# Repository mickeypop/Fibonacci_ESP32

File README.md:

# Fibonacci Clock with ESP32 WiFi
ESP32 Atomic Fibonacci Clock with Android App and full Daylight Savings Time(DST) support

Unlike other Fibonacci Clocks, this is fully Atomic.  
Just set WiFi and a few presets with the first Arduino preset sketch to set preferances then compile the main sketch.

I also gave it minute accuracy, most Fibonacci Clocks can only show within 5 minutes.  4 Extra LEDs place the minutes that do not end in 0 or 5.

I added I2C LCD support for debugging but is not needed in use.

With mDNS support you can access it by web page or Android app as **fibonacci.local** once it is on your WiFi network.

Just choose your Time Zone and the DST rule that applies to you and the clock time is set.

Because I used the preferances library this will not work on the ESP8266 but with the Preferances replaced with file system and say JSON this could be adapted easily.

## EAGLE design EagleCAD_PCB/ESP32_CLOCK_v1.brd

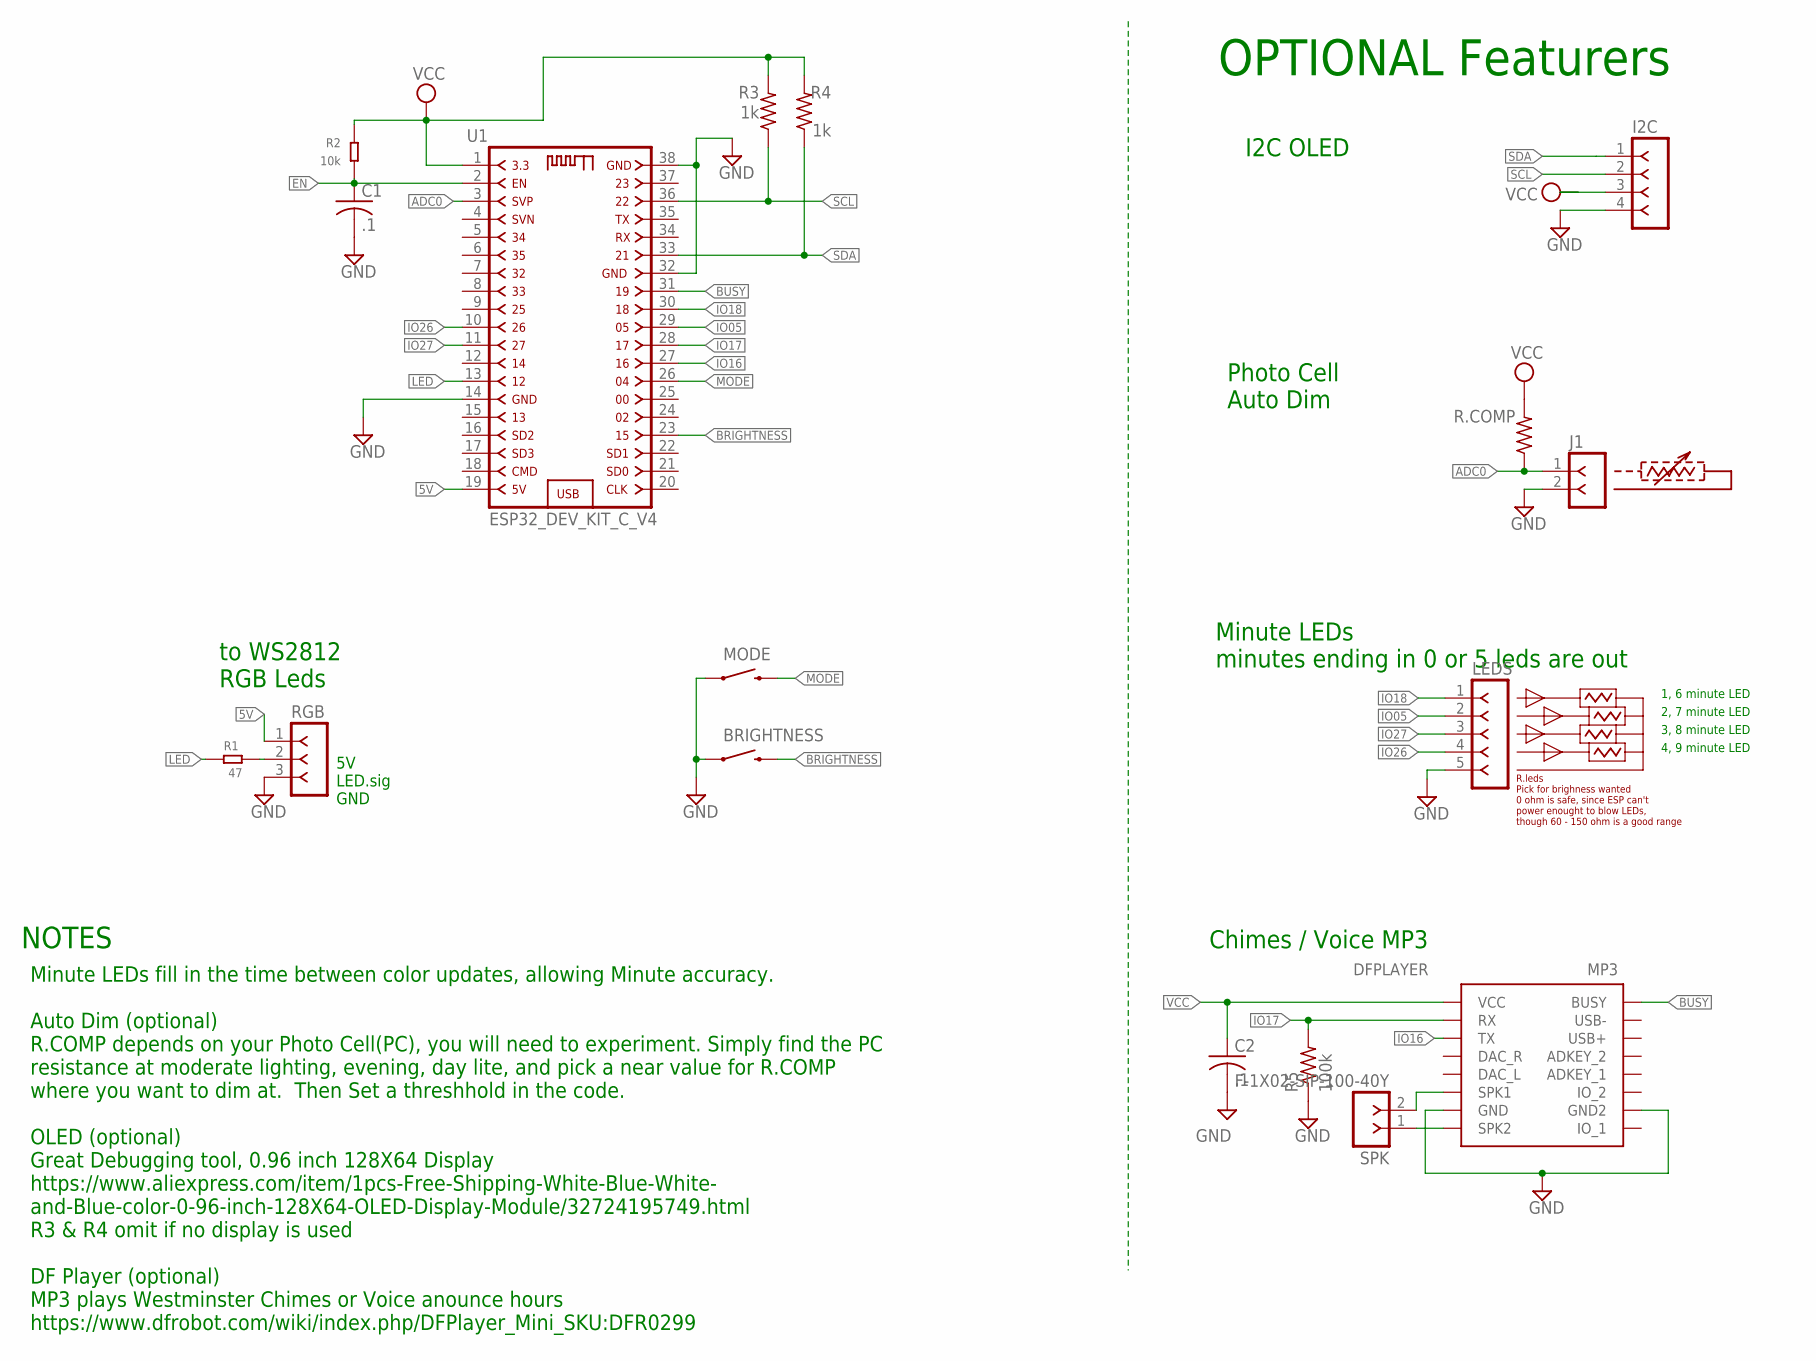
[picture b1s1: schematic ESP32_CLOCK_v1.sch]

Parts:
BRIGHTNESS: SWITCH-MOMENTARY-2SIDE_EZ; TACTILE-PTH-SIDEEZ
C1, C2: .1; C0805K
I2C: F-1X04-SIP-100-40Y; SIP-100-04-40Y
J1: F-1X02-SIP-100-40Y; SIP-100-02-40Y
LEDS: F-1X05-SIP-100-40Y; SIP-100-05-40Y
MODE: SWITCH-MOMENTARY-2SIDE_EZ; TACTILE-PTH-SIDEEZ
MP3: DFPLAYER
R1: 47; R0805
R2: 10k; R0805
R3, R4: 1k; M0805
R5: 100k; M0805
R.COMP: R-US_M0805; M0805
RGB: F-1X03-SIP-100-40Y; SIP-100-03-40Y
SPK: F-1X02-SIP-100-40Y; SIP-100-02-40Y
U1: ESP32_DEV_KIT_C_V4

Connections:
5V: RGB.1, U1.19
ADC0: J1.1, R.COMP.1, U1.3
BRIGHTNESS: BRIGHTNESS.2, U1.23
BUSY: MP3.BUSY, U1.31
EN: C1.1, R2.1, U1.2
GND: BRIGHTNESS.1, C1.2, C2.2, I2C.4, J1.2, LEDS.5, MODE.1, MP3.GND, MP3.GND2, R5.1, RGB.3, U1.14, U1.32, U1.38
IO05: LEDS.2, U1.29
IO16: MP3.TX, U1.27
IO17: MP3.RX, R5.2, U1.28
IO18: LEDS.1, U1.30
IO26: LEDS.4, U1.10
IO27: LEDS.3, U1.11
LED: R1.2, U1.13
MODE: MODE.2, U1.26
unnamed: MP3.SPK2, SPK.1
unnamed: MP3.SPK1, SPK.2
unnamed: R1.1, RGB.2
SCL: I2C.2, R3.1, U1.36
SDA: I2C.1, R4.1, U1.33
VCC: C2.1, I2C.3, MP3.VCC, R2.2, R3.2, R4.2, R.COMP.2, U1.1

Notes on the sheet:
to WS2812 RGB Leds
5V LED.sig GND
1, 6 minute LED
2, 7 minute LED
3, 8 minute LED
4, 9 minute LED
OPTIONAL Featurers
I2C OLED
Photo Cell Auto Dim
R.leds Pick for brighness wanted 0 ohm is safe, since ESP can't power enought to blow LEDs, though 60 - 150 ohm is a good range
Minute LEDs minutes ending in 0 or 5 leds are out
Chimes / Voice MP3
NOTES
Minute LEDs fill in the time between color updates, allowing Minute accuracy. Auto Dim (optional) R.COMP depends on your Photo Cell(PC), you will need to experiment. Simply find the PC resistance at moderate lighting, evening, day lite, and pick a near value for R.COMP where you want to dim at. The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

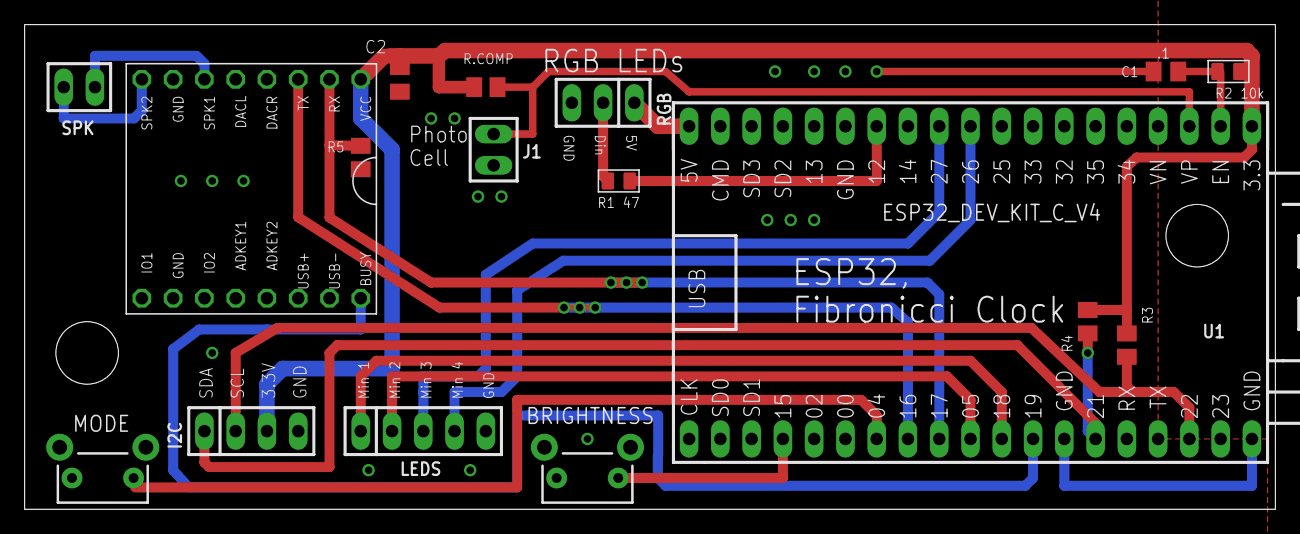
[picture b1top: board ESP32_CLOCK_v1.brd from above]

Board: 2 copper layers, 101.6 x 39.4 mm, 17 parts (0 on the bottom side), 20 nets.

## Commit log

2019-03-19 initial files
2019-03-19 Update README.md
    added better instruction proceedure
2019-03-19 Update README.md
    Fixed typos and updated
2019-03-19 Add files via upload
    added DS file sort program
2019-03-19 Add files via upload
    eagle files added
2019-03-19 Update README.md
    more updates
2020-12-12 Add files via upload
    added code
2020-12-12 Rename DF_PLAYER.ino to df_player.ino

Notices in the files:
parts and their libraries:
con-headers-jp: Copyright (C) 2008, Bob Starr
SparkFun-Electromechanical: Licensing: Creative Commons ShareAlike 4.0 International - https://creativecommons.org/licenses/by-sa/4.0
